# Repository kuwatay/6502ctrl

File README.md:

# 6502ctrl
AVR-based supervisor for a w65c02 microcomputer based on z80ctrl https://github.com/jblang/z80ctrl

6502ctrl has the following features:
* Support W65C02 and 64KB(128KB) ram
* Console and other I/O are handled by DMA (ultra fast WAI instruction)
* Monitor with file management, memory inspector, and built-in 6502 disassembler
* Single-step debugging, breakpoints, and watchpoints to trace 6502 bus activity in real-time
* Arduino Shield style hardware (6502ctrl-mega)
* Flexible MIT-licensed firmware inhelited from z80ctrl

# Documentation

## Application
https://github.com/kuwatay/6502ctrl/wiki/Application

## Hardware note
https://github.com/kuwatay/6502ctrl/wiki/Hardware-of-6502ctrl-mega

## Supervisor sample session
https://github.com/kuwatay/6502ctrl/wiki/Sample-session-of--Supervisor

## DMA handling
https://github.com/kuwatay/6502ctrl/wiki/DMA-I-O-request

## MIT license
Permission is hereby granted, free of charge, to any person obtaining a copy of this software and associated documentation files (the "Software"), to deal in the Software without restriction, including without limitation the rights to use, copy, modify, merge, publish, distribute, sublicense, and/or sell copies of the Software, and to permit persons to whom the Software is furnished to do so, subject to the following conditions:

The above copyright notice and this permission notice shall be included in all copies or substantial portions of the Software.

THE SOFTWARE IS PROVIDED "AS IS", WITHOUT WARRANTY OF ANY KIND, EXPRESS OR IMPLIED, INCLUDING BUT NOT LIMITED TO THE WARRANTIES OF MERCHANTABILITY, FITNESS FOR A PARTICULAR PURPOSE AND NONINFRINGEMENT. IN NO EVENT SHALL THE AUTHORS OR COPYRIGHT HOLDERS BE LIABLE FOR ANY CLAIM, DAMAGES OR OTHER LIABILITY, WHETHER IN AN ACTION OF CONTRACT, TORT OR OTHERWISE, ARISING FROM, OUT OF OR IN CONNECTION WITH THE SOFTWARE OR THE USE OR OTHER DEALINGS IN THE SOFTWARE.

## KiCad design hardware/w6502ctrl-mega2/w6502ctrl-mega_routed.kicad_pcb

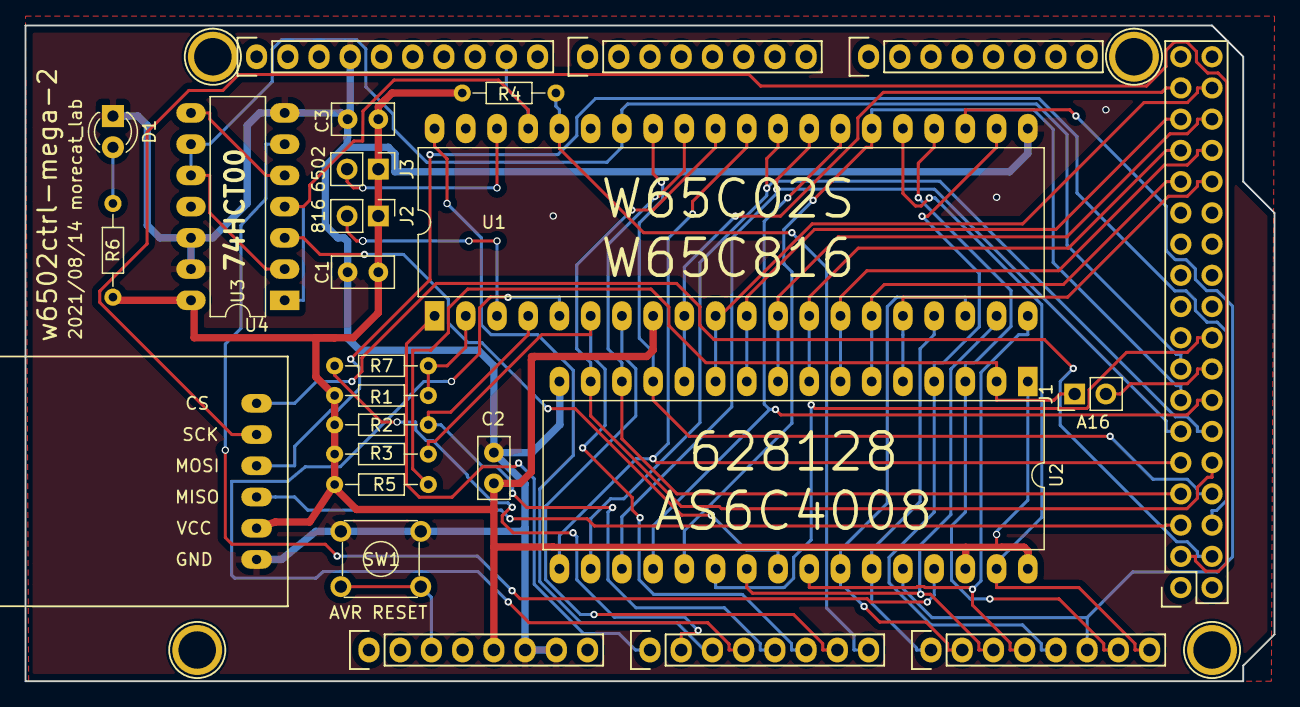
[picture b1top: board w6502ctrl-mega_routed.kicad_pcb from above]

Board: 2 copper layers, 101.6 x 53.3 mm, 30 parts (0 on the bottom side), 51 nets.

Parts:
C1, C2, C3: 100nF; C_Disc_D5.0mm_W2.5mm_P2.50mm
D1: LED; LED_D3.0mm
J1: Conn_01x02_Female; Pin_Header_Straight_1x02_Pitch2.54mm
J2: 816; Pin_Header_Straight_1x02_Pitch2.54mm
J3: 6502; Pin_Header_Straight_1x02_Pitch2.54mm
P1: Digital; Socket_Strip_Arduino_2x18
P2: Power; Socket_Strip_Arduino_1x08
P3, P4: Analog; Socket_Strip_Arduino_1x08
P5: PWM; Socket_Strip_Arduino_1x10
P6: PWM; Socket_Strip_Arduino_1x08
P7: Communication; Socket_Strip_Arduino_1x08
P8, P10, P11, P13: CONN_01X01; Arduino_1pin
R1, R2, R4, R7: 3.3k; R_Axial_DIN0204_L3.6mm_D1.6mm_P7.62mm_Horizontal
R3: 3.3K; R_Axial_DIN0204_L3.6mm_D1.6mm_P7.62mm_Horizontal
R5: 10k; R_Axial_DIN0204_L3.6mm_D1.6mm_P7.62mm_Horizontal
R6: 1k; R_Axial_DIN0204_L3.6mm_D1.6mm_P7.62mm_Horizontal
SW1: SW_MEC_5E; SW_TH_Tactile_Omron_B3F-10xx
U1: W65C02/816; DIP-40_W15.24mm_LongPads
U2: AS6C4008; DIP-32_W15.24mm_LongPads
U3: 74HC00; DIP-14_W7.62mm_LongPads
U4: MicroCardAdapter; MicroSDCardAdapter

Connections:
+5V: C1.1, C2.1, C3.1, J2.1, J3.1, P2.5, R1.1, R2.1, R3.1, R4.1, R5.2, R6.1, U1.8, U2.1, U2.30, U2.32, U3.14, U4.5
A0: P1.33, U1.9, U2.12
A1: P1.34, U1.10, U2.11
A2: P1.31, U1.11, U2.10
A3: P1.32, U1.12, U2.9
A4: P1.29, U1.13, U2.8
A5: P1.30, U1.14, U2.7
A6: P1.27, U1.15, U2.6
A7: P1.28, U1.16, U2.5
A8: P4.1, U1.17, U2.27
A9: P4.2, U1.18, U2.26
A10: P4.3, U1.19, U2.23
A11: P4.4, U1.20, U2.25
A12: P4.5, U1.22, U2.4
A13: P4.6, U1.23, U2.28
A14: P4.7, U1.24, U2.3
A15: P4.8, U1.25, U2.31
A16: J1.2, P1.16
AVR_RESET: P2.3, SW1.3, SW1.4
BE: P3.8, R4.2, U1.36
D0: P1.8, U1.33, U2.13
D1: P1.7, U1.32, U2.14
D2: P1.10, U1.31, U2.15
D3: P1.9, U1.30, U2.17
D4: P1.12, U1.29, U2.18
D5: P1.11, U1.28, U2.19
D6: P1.14, U1.27, U2.20
D7: P1.13, U1.26, U2.21
GND: C1.2, C2.2, C3.2, D1.1, P2.6, P2.7, P5.4, SW1.1, SW1.2, U1.21, U2.16, U3.7, U3.12, U3.13, U4.6
IRQ: P3.5, R2.2, U1.4
MISO: P1.5, U4.4
ML: P3.4, U1.5
MOSI: P1.6, U4.3
NMI: P3.6, R3.2, U1.6
unnamed: D1.2, R6.2
unnamed: J1.1, R5.1, U2.2
unnamed: J2.2, U1.3
unnamed: J3.2, U1.38
unnamed: R1.2, R7.1, U1.2
unnamed: U2.24, U3.3
unnamed: U2.29, U3.6
unnamed: U3.5, U3.8
PHI2: P5.9, U1.37, U3.1, U3.4
RAME: P1.18, U2.22
RDY: P3.2, R7.2
RESET: P3.3, U1.40
RW: P1.15, U1.34, U3.2, U3.9, U3.10
SCK: P1.3, U4.2
SS: P1.4, U4.1
SYNC: P3.7, U1.7
VP: P3.1, U1.1

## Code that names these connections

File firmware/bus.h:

/* 6502ctrl (https://github.com/kuwatay/6502cttl)
 * Copyright 2021 Yoshitaka Kuwata a.k.a. morecat_lab
 *
 * based on z80ctrl (https://github.com/jblang/z80ctrl)
 * Copyright 2018 J.B. Langston
 *
 * Permission is hereby granted, free of charge, to any person obtaining a 
 * copy of this software and associated documentation files (the "Software"), 
 * to deal in the Software without restriction, including without limitation 
 * the rights to use, copy, modify, merge, publish, distribute, sublicense, 
 * and/or sell copies of the Software, and to permit persons to whom the 
 * Software is furnished to do so, subject to the following conditions:
 * 
 * The above copyright notice and this permission notice shall be included in
 * all copies or substantial portions of the Software.
 * 
 * THE SOFTWARE IS PROVIDED "AS IS", WITHOUT WARRANTY OF ANY KIND, EXPRESS OR
 * IMPLIED, INCLUDING BUT NOT LIMITED TO THE WARRANTIES OF MERCHANTABILITY, 
 * FITNESS FOR A PARTICULAR PURPOSE AND NONINFRINGEMENT. IN NO EVENT SHALL THE
 * AUTHORS OR COPYRIGHT HOLDERS BE LIABLE FOR ANY CLAIM, DAMAGES OR OTHER 
 * LIABILITY, WHETHER IN AN ACTION OF CONTRACT, TORT OR OTHERWISE, ARISING 
 * FROM, OUT OF OR IN CONNECTION WITH THE SOFTWARE OR THE USE OR OTHER 
 * DEALINGS IN THE SOFTWARE.
 */

/**
 * @file bus.h Low-level control of the Z80 bus
 */

#ifndef BUS_H
#define BUS_H

#include <avr/io.h>

/**
 * Address Bus
 */

#define ADDRLO_DDR DDRA
#define ADDRLO_PORT PORTA
#define ADDRLO_PIN PINA

#ifdef MEGA
#define ADDRHI_DDR DDRK
#define ADDRHI_PORT PORTK
#define ADDRHI_PIN PINK
#else
#define ADDRHI_DDR DDRC
#define ADDRHI_PORT PORTC
#define ADDRHI_PIN PINC
#endif

#define ADDR_INPUT (ADDRLO_DDR = 0x00, ADDRHI_DDR = 0x00)
#define ADDR_OUTPUT (ADDRLO_DDR = 0xFF, ADDRHI_DDR = 0xff)

#define GET_ADDRLO ADDRLO_PIN
#define SET_ADDRLO(addr) ADDRLO_PORT = (addr)

#define GET_ADDRHI ADDRHI_PIN
#define SET_ADDRHI(addr) ADDRHI_PORT = (addr)

#define GET_ADDR (GET_ADDRLO | (GET_ADDRHI << 8))
#define SET_ADDR(addr) (SET_ADDRLO((addr) & 0xFF), SET_ADDRHI((addr) >> 8))

/**
 * Data Bus
 */

#define DATA_DDR DDRL
#define DATA_PORT PORTL
#define DATA_PIN PINL

#define DATA_INPUT DATA_DDR = 0x00
#define DATA_OUTPUT DATA_DDR = 0xFF
#define GET_DATA DATA_PIN
#define SET_DATA(data) DATA_PORT = (data)

/**
 * PORTG Flags
 */
#define RAME (1 << 2)
#define RAME_HI PORTG |= RAME
#define RAME_LO PORTG &= ~RAME
#define RAME_OUTPUT DDRG |= RAME
#define RAME_INPUT DDRG &= ~RAME
#define RAME_STATUS (status.flags2 & RAME)

#define RW (1 << 1)
#define GET_RW (PING & RW)
#define RW_HI PORTG |= RW
#define RW_LO PORTG &= ~RW
#define RW_OUTPUT DDRG |= RW
#define RW_INPUT DDRG &= ~RW
#define RW_STATUS (status.flags2 & RW)

#define CTRLG_OUTPUT_INIT DDRG |= (RW | RAME)
#define CTRLG_MASK (RAME | RW)
/**
 * CONTROL_PORT Flags
 */
#ifdef MEGA
// Arduino Mega Shield version
#define CONT_PORT PORTF
#define CONT_DDR  DDRF
#define CONT_PIN  PINF
#else
// BREADBOARD VERSION USE PORTK
#define CONT_PORT PORTK
#define CONT_DDR  DDRK
#define CONT_PIN  PINK
#endif

#define VP (1 << 0)
#define GET_VP (CONT_PIN & VP)
#define VP_INPUT CONT_DDR &= ~VP
#define VP_STATUS (status.flags & VP)

#define RDY (1 << 1)
#define GET_RDY (CONT_PIN & RDY)
#define RDY_HI CONT_PORT |= RDY
#define RDY_LO CONT_PORT &= ~RDY
#define RDY_OUTPUT CONT_DDR |= RDY
#define RDY_INPUT CONT_DDR &= ~RDY
#define RDY_STATUS (status.flags & RDY)

#define RESET (1 << 2)
#define GET_RESET (CONT_PIN & RESET)
#define RESET_HI CONT_PORT |= RESET
#define RESET_LO CONT_PORT &= ~RESET
#define RESET_OUTPUT CONT_DDR |= RESET
#define RESET_INPUT CONT_DDR &= ~RESET
#define RESET_STATUS (status.flags & RESET)

#define MLB (1 << 3)
#define GET_MLB (CONT_PIN & MLB)
#define MLB_INPUT CONT_DDR &= ~MLB
#define MLB_STATUS (status.flags & MLB)

#define IRQ (1 << 4)
#define GET_IRQ (CONT_PIN & IRQ)
#define IRQ_HI CONT_PORT |= IRQ
#define IRQ_LO CONT_PORT &= ~IRQ
#define IRQ_OUTPUT CONT_DDR |= IRQ
#define IRQ_INPUT CONT_DDR &= ~IRQ
#define IRQ_STATUS (status.flags & IRQ)

#define NMI (1 << 5)
#define GET_NMI (CONT_PIN & NMI)
#define NMI_HI CONT_PORT |= NMI
#define NMI_LO CONT_PORT &= ~NMI
#define NMI_OUTPUT CONT_DDR |= NMI
#define NMI_INPUT CONT_DDR &= ~NMI
#define NMI_STATUS (status.flags & NMI)

#define SYNC (1 << 6)
#define GET_SYNC (CONT_PIN & SYNC)
#define SYNC_INPUT CONT_DDR &= ~SYNC
#define SYNC_STATUS (status.flags & SYNC)

#define BE (1 << 7)
#define GET_BE (CONT_PIN & BE)
#define BE_HI CONT_PORT |= BE
#define BE_LO CONT_PORT &= ~BE
#define BE_OUTPUT CONT_DDR |= BE
#define BE_INPUT CONT_DDR &= ~BE
#define BE_STATUS (status.flags & BE)

#define CTRLK_OUTPUT_INIT CONT_DDR |= (RESET | BE)


/* PORT H */
#define PHI2 (1 << 6)
#define GET_PHI2 (PINH & PHI2)
#define PHI2_HI PORTH |= PHI2
#define PHI2_LO PORTH &= ~PHI2
#define PHI2_TOGGLE PINH |= PHI2
#define PHI2_STATUS (status.flags2 & PHI2)

#define CTRLH_OUTPUT_INIT DDRH |= PHI2
#define CTRLH_MASK PHI2
#define GET_BUSACK (0) // DUMMY

/**
 * Complete bus status all in one place
 */
typedef struct {
        uint8_t flags;
        uint8_t flags2;
        uint16_t addr;
        uint8_t data;
} bus_stat;

extern uint8_t clkdiv;
extern uint32_t base_addr;

void clk_cycle(uint8_t cycles);
void clk_run(void);
void clk_stop(void);

uint8_t bus_request(void);
void bus_release(void);
void bus_init(void);

bus_stat bus_status(void);
bus_stat bus_status_fast(void);
void bus_log(bus_stat status);

uint8_t io_out(uint8_t addr, uint8_t value);
uint8_t io_in(uint8_t addr);

#if defined(BANK_PORT) || defined(BANK_BASE)
void mem_bank(uint8_t bank, uint8_t page);
void mem_bank_addr(uint32_t addr);
#else
#define mem_bank(bank, page)
#define mem_bank_addr(addr)
#endif

typedef void (*pagefunc_t)(uint8_t, uint8_t, void*);
void mem_read_page(uint8_t start, uint8_t end, void *buf);
void mem_write_page(uint8_t start, uint8_t end, void *buf);
void mem_write_page_P(uint8_t start, uint8_t end, void *buf);
void mem_iterate(uint16_t start, uint16_t end, pagefunc_t dopage, void *buf);
void mem_iterate_banked(uint32_t start, uint32_t end, pagefunc_t dopage, void *buf);

#define mem_read(addr, buf, len) mem_iterate((addr), ((addr) + ((len) - 1)), mem_read_page, (buf));
#define mem_write(addr, buf, len) mem_iterate((addr), ((addr) + ((len) - 1)), mem_write_page, (buf));
#define mem_write_P(addr, buf, len) mem_iterate((addr), ((addr) + ((len) - 1)), mem_write_page_P, (void *)(buf));

#define mem_read_banked(addr, buf, len) mem_iterate_banked((addr), ((addr) + ((len) - 1)), mem_read_page, (buf));
#define mem_write_banked(addr, buf, len) mem_iterate_banked((addr), ((addr) + ((len) - 1)), mem_write_page, (buf));
#define mem_write_banked_P(addr, buf, len) mem_iterate_banked((addr), ((addr) + ((len) - 1)), mem_write_page_P, (void *)(buf));


#endif

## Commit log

2021-07-13 upload hardware and examples
2021-07-16 upload unimon
2021-07-22 add OSI_BASIC
2021-07-22 upload binary
2021-07-24 fix bus.s for mega pin assign
    adjust pin assign for 6502ctrl-mega
2021-08-16 upload rev2 hardware
2021-08-16 update rev2 hardware
    update rev2 hardware
2021-08-16 change location of zip file
    change location of zip file
2021-08-26 add HPDL1414 display support
    add HPDL1414 display shield support
    spell correction
2021-08-26 delete hpdl1414 test code
    delete hpdl1414 test code
2021-08-29 remove debug code
2021-08-31 add initialize BE
2021-09-02 arrange folder & upload rev2b schematic
2021-09-02 redo rename
2021-09-02 rename files
2021-09-02 add picture of rev1 modification
2021-09-06 add example of unimon session
2021-09-06 add rev2 board images
2021-09-06 Update README.md
    update to rev2 image
2021-09-12 add object file
    add object file
2021-11-04 Create 6502ctrl-57600.hex
    add 57.6K baud version
2025-04-29 change startup message
    change startup message
